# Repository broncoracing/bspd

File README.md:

# BSPD 
Bronco Racing Brake System Plausibility Device

Note: with the "no latch" option selected on the jumpers the output is inverted :(

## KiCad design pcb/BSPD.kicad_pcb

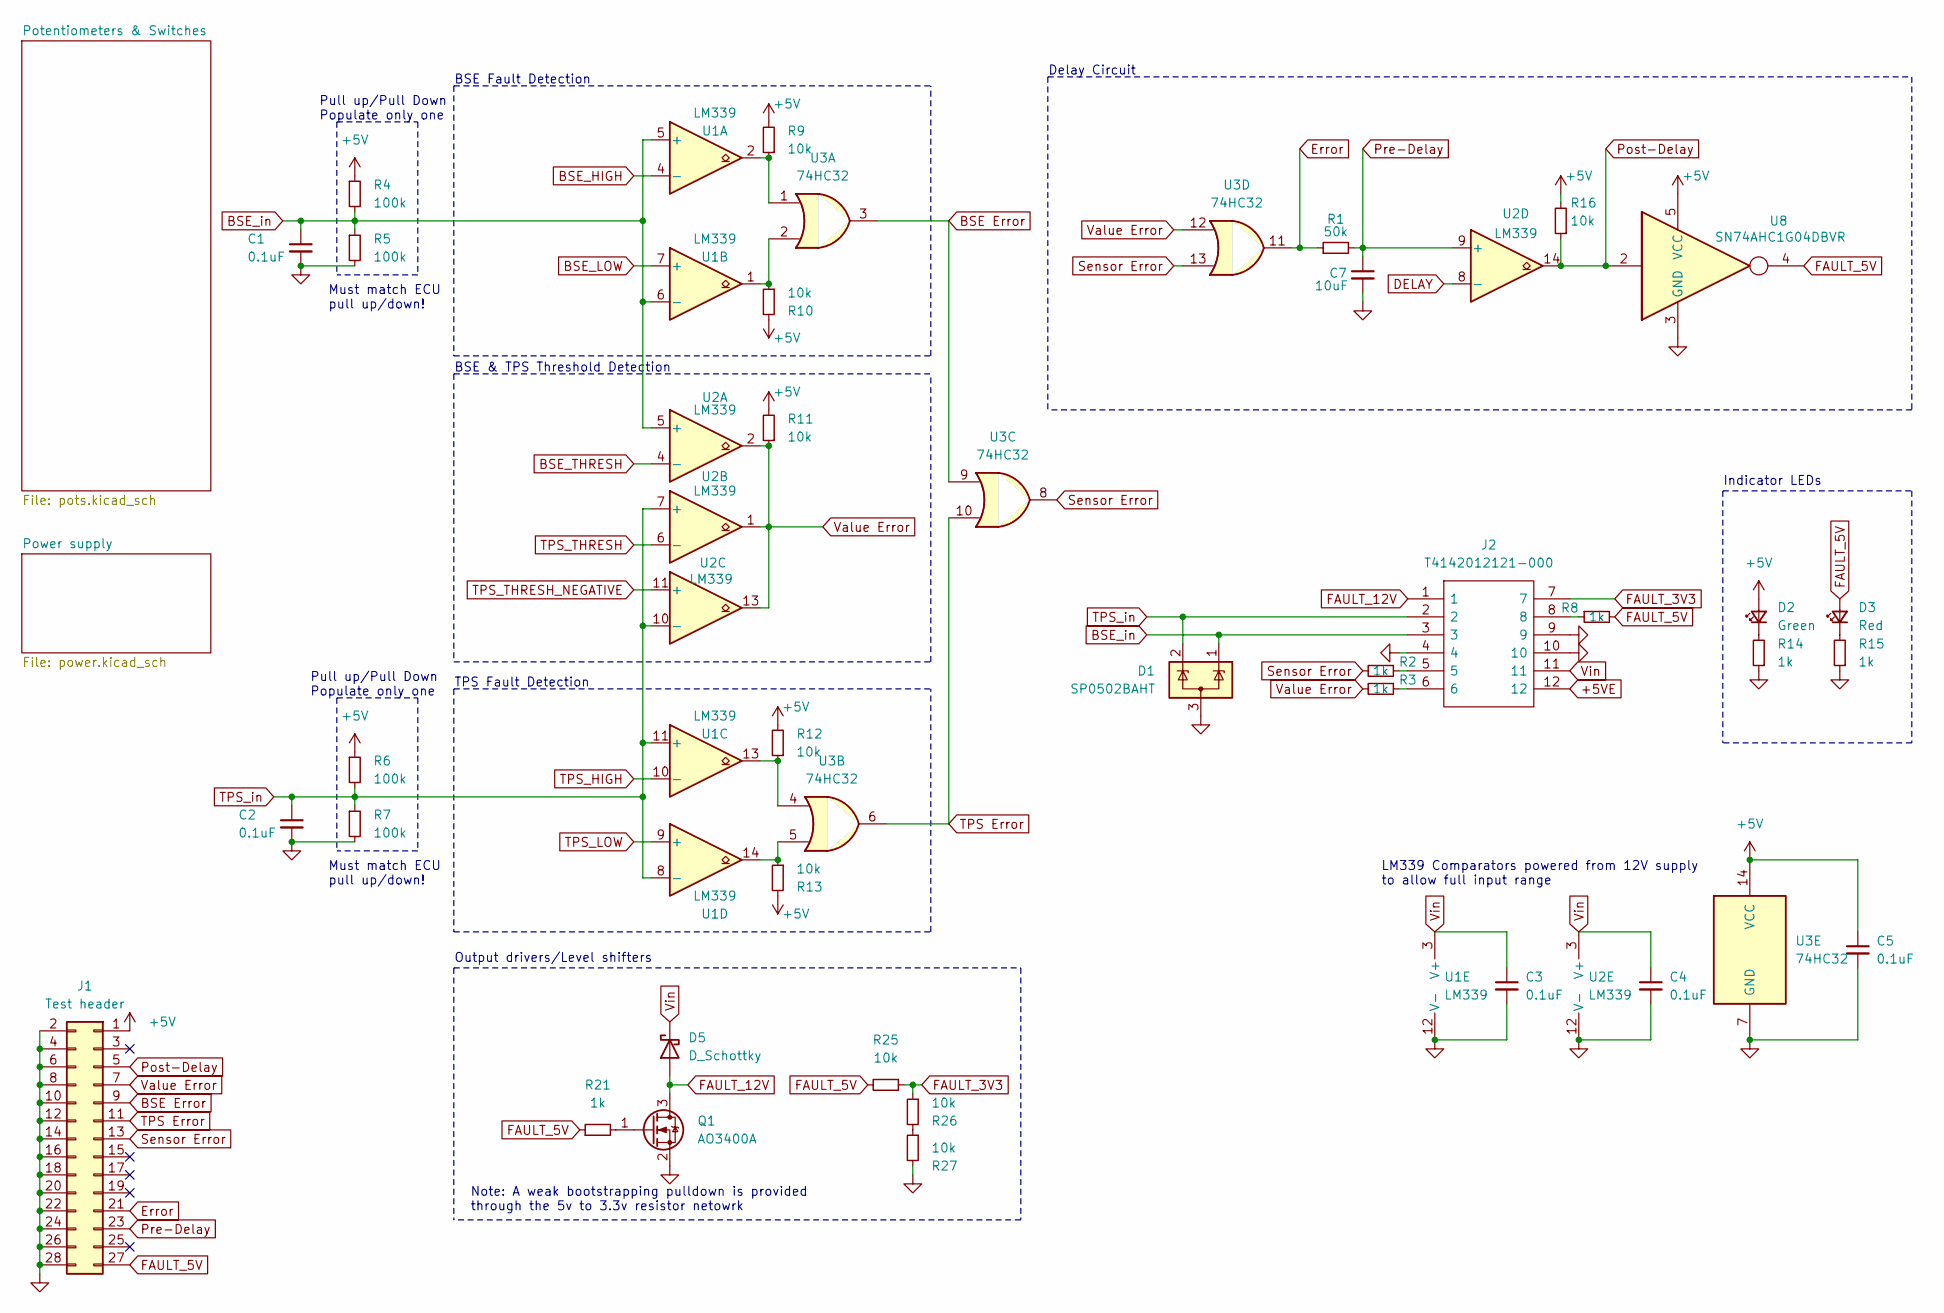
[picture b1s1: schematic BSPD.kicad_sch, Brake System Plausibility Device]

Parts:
C1, C2, C3, C4, C5: 0.1uF; C_0402_1005Metric; LCSC C307331
C7: 10uF; C_0805_2012Metric; LCSC C440198
D1: SP0502BAHT; SOT-23; LCSC C32677
D2: Green; LED_0603_1608Metric; LCSC C2986059
D3: Red; LED_0603_1608Metric; LCSC C2286
D5: D_Schottky; D_SOD-323; LCSC C191023
J1: Test header; PinHeader_2x14_P2.54mm_Vertical
J2: T4142012121-000; T4140012121000; Mouser Part Number 571-T4142012121-000
Q1: AO3400A; SOT-23; LCSC C20917
R1: 50k; R_0402_1005Metric; LCSC C166559
R2, R3, R8, R14, R15, R21: 1k; R_0402_1005Metric; LCSC C11702
R4, R5, R6, R7: 100k; R_0402_1005Metric; LCSC C25741
R9, R10, R11, R12, R13, R16, R25, R26, R27: 10k; R_0402_1005Metric; LCSC C25744
U1, U2: LM339; SOIC-14_3.9x8.7mm_P1.27mm; LCSC C63821
U3: 74HC32; SOIC-14_3.9x8.7mm_P1.27mm; LCSC C6838
U8: SN74AHC1G04DBVR; SOT-23-5; LCSC C7465

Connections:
+5V: C5.1, D2.2 (A), J1.1, R4.1, R6.1, R9.2, R10.2, R11.2, R12.2, R13.2, R16.2, U3.14 (VCC), U8.5 (VCC); also elsewhere on the board
+5VE: J2.12; also elsewhere on the board
BSE Error: J1.9, U3.3, U3.9
BSE_HIGH: U1.4 (-); also elsewhere on the board
BSE_LOW: U1.7 (+); also elsewhere on the board
BSE_THRESH: U2.4 (-); also elsewhere on the board
BSE_in: C1.1, D1.1 (K), J2.3, R4.2, R5.1, U1.5 (+), U1.6 (-), U2.5 (+)
DELAY: U2.8 (-); also elsewhere on the board
Error: J1.21, R1.1, U3.11
FAULT_3V3: J2.7, R25.1, R26.1
FAULT_5V: D3.2 (A), J1.27, R8.2, R21.1, R25.2, U8.4
FAULT_12V: D5.2 (A), J2.1, Q1.3 (D)
GND: C1.2, C2.2, C3.2, C4.2, C5.2, C7.2, D1.3 (A), J1.2, J1.4, J1.6, J1.8, J1.10, J1.12, J1.14, J1.16, J1.18, J1.20, J1.22, J1.24, J1.26, J1.28, J2.4, J2.9, J2.10, Q1.2 (S), R5.2, R7.2, R14.1, R15.1, R27.2, U1.12 (V-), U2.12 (V-), U3.7 (GND), U8.3 (GND); also elsewhere on the board
unnamed: D2.1 (K), R14.2
unnamed: D3.1 (K), R15.2
unnamed: J2.5, R2.1
unnamed: J2.6, R3.1
unnamed: J2.8, R8.1
unnamed: Q1.1 (G), R21.2
unnamed: R9.1, U1.2, U3.1
unnamed: R10.1, U1.1, U3.2
unnamed: R12.1, U1.13, U3.4
unnamed: R13.1, U1.14, U3.5
unnamed: R26.2, R27.1
Post-Delay: J1.5, R16.1, U2.14, U8.2
Pre-Delay: C7.1, J1.23, R1.2, U2.9 (+)
Sensor Error: J1.13, R2.2, U3.8, U3.13
TPS Error: J1.11, U3.6, U3.10
TPS_HIGH: U1.10 (-); also elsewhere on the board
TPS_LOW: U1.9 (+); also elsewhere on the board
TPS_THRESH: U2.6 (-); also elsewhere on the board
TPS_THRESH_NEGATIVE: U2.11 (+); also elsewhere on the board
TPS_in: C2.1, D1.2 (K), J2.2, R6.2, R7.1, U1.8 (-), U1.11 (+), U2.7 (+), U2.10 (-)
Value Error: J1.7, R3.2, R11.1, U2.1, U2.2, U2.13, U3.12
Vin: C3.1, C4.1, D5.1 (K), J2.11, U1.3 (V+), U2.3 (V+); also elsewhere on the board

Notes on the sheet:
Pull up/Pull Down Populate only one
Delay Circuit
TPS Fault Detection
LM339 Comparators powered from 12V supply to allow full input range
Must match ECU pull up/down!
Indicator LEDs
Output drivers/Level shifters
BSE Fault Detection
BSE & TPS Threshold Detection
Note: A weak bootstrapping pulldown is provided through the 5v to 3.3v resistor netowrk

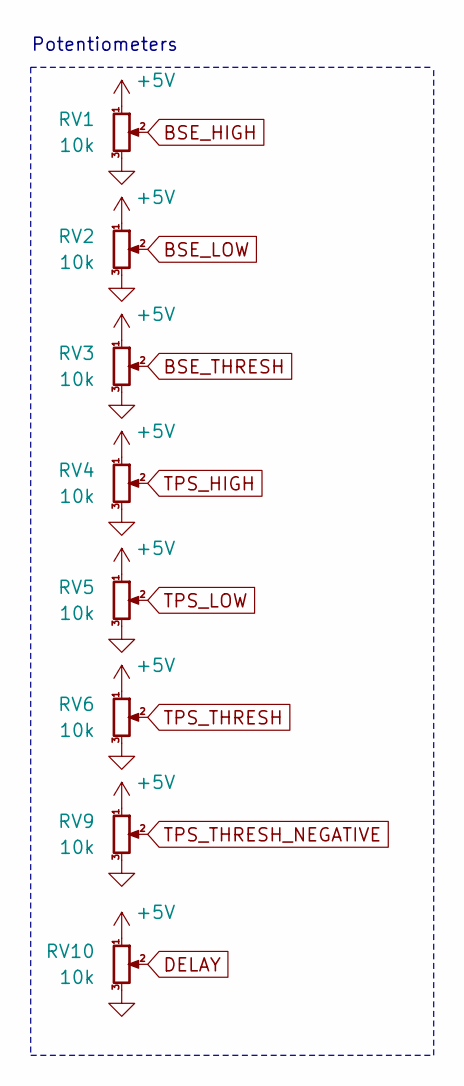
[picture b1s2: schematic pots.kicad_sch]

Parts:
RV1, RV2, RV3, RV4, RV5, RV6, RV9, RV10: 10k; Potentiometer_Bourns_TC33X_Vertical; LCSC C719176

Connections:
+5V: RV1.1, RV2.1, RV3.1, RV4.1, RV5.1, RV6.1, RV9.1, RV10.1; also elsewhere on the board
BSE_HIGH: RV1.2; also elsewhere on the board
BSE_LOW: RV2.2; also elsewhere on the board
BSE_THRESH: RV3.2; also elsewhere on the board
DELAY: RV10.2; also elsewhere on the board
GND: RV1.3, RV2.3, RV3.3, RV4.3, RV5.3, RV6.3, RV9.3, RV10.3; also elsewhere on the board
TPS_HIGH: RV4.2; also elsewhere on the board
TPS_LOW: RV5.2; also elsewhere on the board
TPS_THRESH: RV6.2; also elsewhere on the board
TPS_THRESH_NEGATIVE: RV9.2; also elsewhere on the board

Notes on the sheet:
Potentiometers

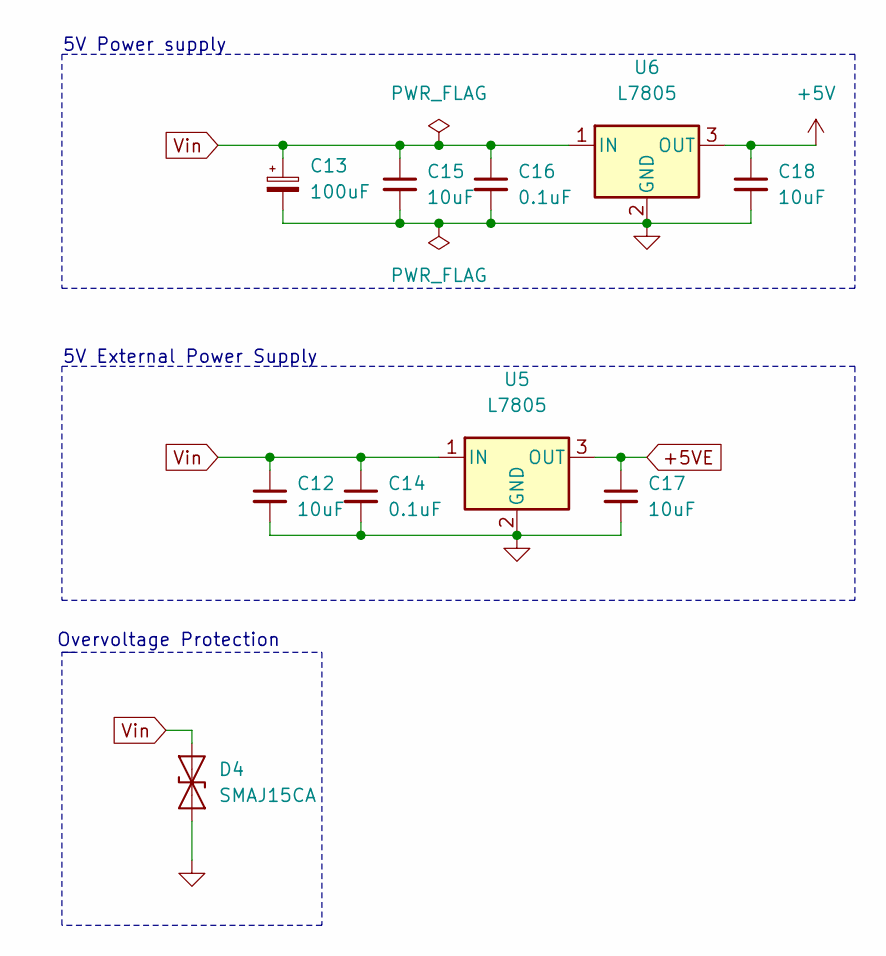
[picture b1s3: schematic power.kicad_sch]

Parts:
C12, C15, C17, C18: 10uF; C_0805_2012Metric; LCSC C440198
C13: 100uF; C_Elec_6.3x7.7; LCSC C2836437
C14, C16: 0.1uF; C_0402_1005Metric; LCSC C307331
D4: SMAJ15CA; D_SMA; LCSC C223985
U5, U6: L7805; TO-252-2; LCSC C897464

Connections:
+5V: C18.1, U6.3 (OUT); also elsewhere on the board
+5VE: C17.1, U5.3 (OUT); also elsewhere on the board
GND: C12.2, C13.2, C14.2, C15.2, C16.2, C17.2, C18.2, D4.1 (A1), U5.2 (GND), U6.2 (GND); also elsewhere on the board
Vin: C12.1, C13.1, C14.1, C15.1, C16.1, D4.2 (A2), U5.1 (IN), U6.1 (IN); also elsewhere on the board

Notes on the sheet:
Overvoltage Protection
5V External Power Supply
5V Power supply

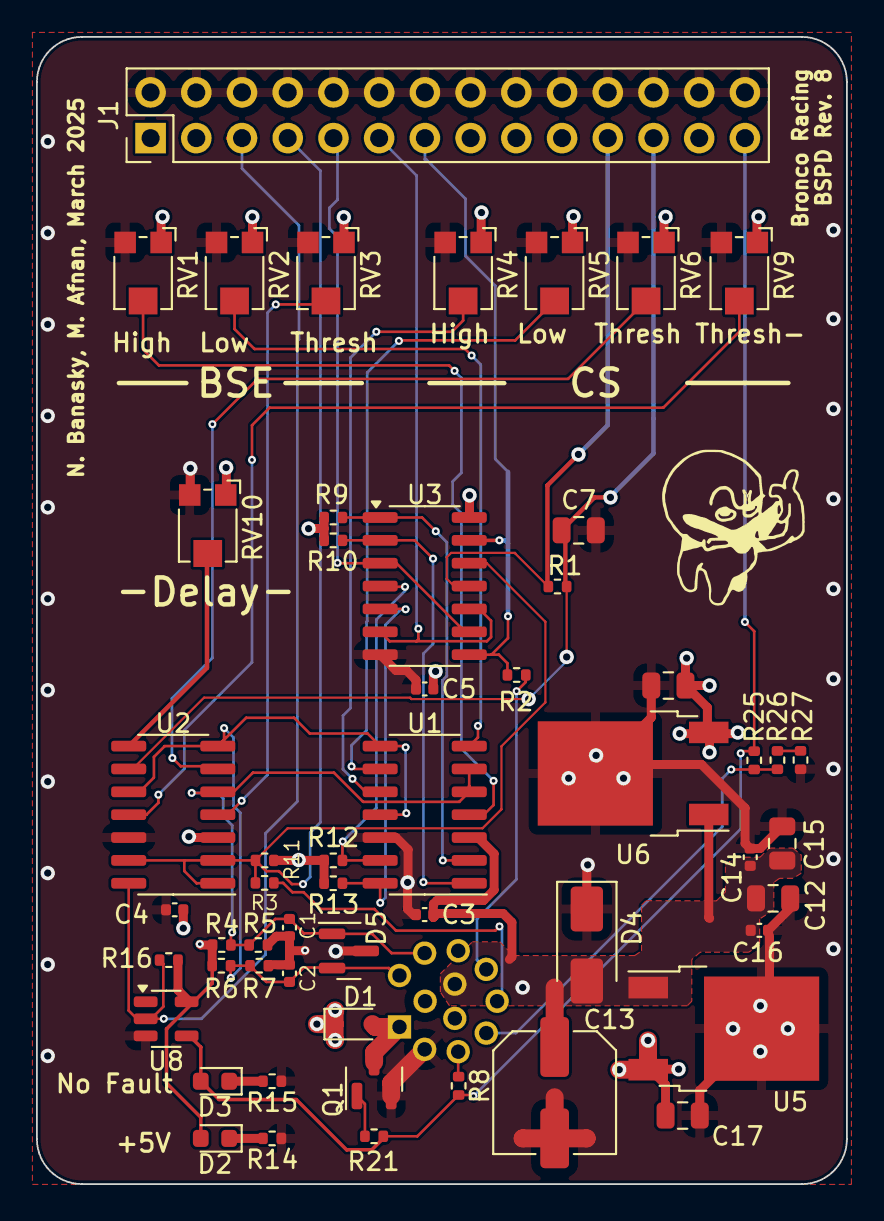
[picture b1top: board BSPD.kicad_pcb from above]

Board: 4 copper layers, 45.0 x 63.7 mm, 55 parts (1 on the bottom side), 35 nets.

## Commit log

2021-02-13 initial commit of V3. Layout not updated
2021-02-17 Updates, need to check traces still
    - added 4 more +5 caps
    - relocated components for better traces
    - still need to go thru and check for bad traces.
2021-02-17 Fixed all the bad traces, no drc or unrouted violation
2021-02-18 Added digikey cart, Relay is backordered
2021-02-20 Fixed ling power and ground via traces. checked every part to confirm power and ground connection.
2021-02-20 shortened some traces
2021-02-20 Version 3 completed and ordered
2021-03-17 Fixed mosfet logic, updated Regulator, Gerbers v4
2021-03-22 Fixed pull up before mosfet
2021-04-01 Updated the V Reg name to correct one
2022-05-25 cleanup useless files, update gitignore
2022-05-25 Remove DS_Store
2022-10-04 Switched to KiCad
2022-10-18 Schematic/layout for new revision
2022-10-18 Fixed kibot again
2022-10-18 Switched to vertical DTM header
2022-10-19 Fix kibot
2022-10-30 Fixed flyback/reverse polarity protection, added part #s
2023-01-26 Switch to M12 Connector, fix comparator issue from rev 5
2023-01-29 Added jlc part number for 7805
2023-01-29 Added jlc part number for dip switches
2023-02-06 Rev6 (#3)
    * Switched to KiCad
    * Schematic/layout for new revision
    * Switched to vertical DTM header
    * Fix kibot
    * Fixed flyback/reverse polarity protection, added part #s
    * Switch to M12 Connector, fix comparator issue from rev 5
2023-08-17 Update to KiCad 7, bump project revision/date
2023-08-17 Update CI for kicad 7
2023-08-17 Fixed violations after kicad version bump
2023-08-17 fix missing footprint
2025-03-06 REV 8 Init
2025-03-06 Update kibot.yml with artifact v4
2025-03-07 Rev 8 MFG artifacts
2025-03-07 Memes and Small Adjustments
